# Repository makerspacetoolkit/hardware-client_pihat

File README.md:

# hardware-client_pihat
Circuit board to support the full machine client as well as simple tool that just need access control.

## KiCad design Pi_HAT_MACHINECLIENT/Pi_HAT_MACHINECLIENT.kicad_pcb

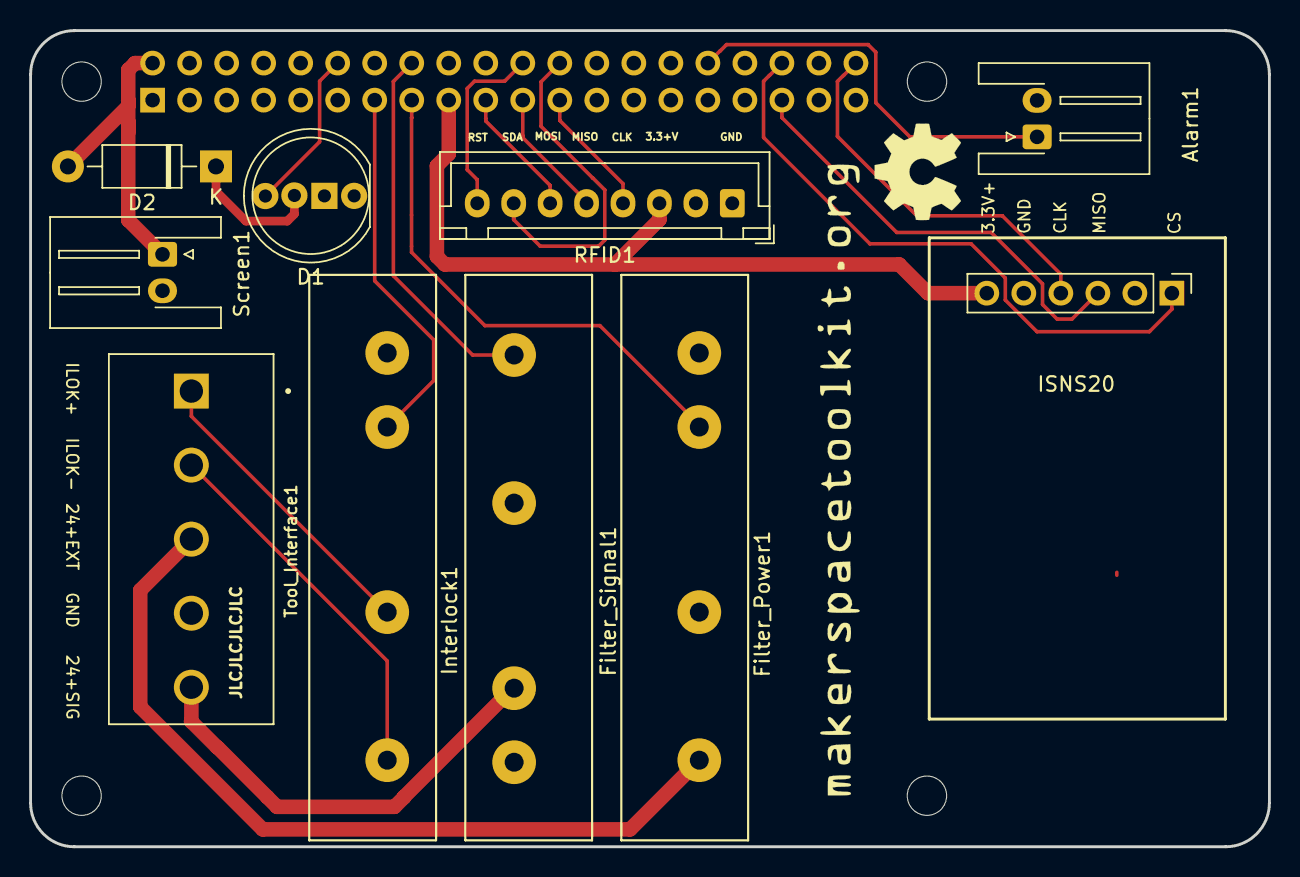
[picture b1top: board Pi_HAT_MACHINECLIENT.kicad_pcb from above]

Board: 2 copper layers, 85.0 x 56.0 mm, 11 parts (1 on the bottom side), 21 nets.

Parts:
Alarm1: Conn_01x02_Male; JST_XH_S02B-XH-A-1_1x02_P2.50mm_Horizontal
D1: WS2812B; LED_D8.0mm-ws2812
D2: 1N4001; D_DO-41_SOD81_P10.16mm_Horizontal
Filter_Power1: SSR-KF0602D; KF0602D
Filter_Signal1: SSR-KF0602D; KF0602D
ISNS20: Conn_01x06_Male; PinHeader_1x06_P2.54mm_Vertical
Interlock1: SSR-KF0602D; KF0602D
J2: Conn_02x20_Odd_Even; PinSocket_2x20_P2.54mm_Vertical
RFID1: Conn_01x08_Male; JST_XH_B08B-XH-A_1x08_P2.50mm_Vertical
Screen1: Conn_01x02_Male; JST_XH_S02B-XH-A-1_1x02_P2.50mm_Horizontal
Tool_Interface1: Screw_Terminal_01x05; CUI_TB010-508-05BE

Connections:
24V_EXT: Filter_Power1.4, Tool_Interface1.3
+3V3: ISNS20.6, J2.17, RFID1.3
+5V: D2.2, J2.2, Screen1.1
+24V: Filter_Signal1.2, Tool_Interface1.5
Alarm: Alarm1.1, J2.32
DIN: D1.4, J2.12
GND: Alarm1.2, D1.1, Filter_Power1.1, Filter_Power1.3, Filter_Signal1.1, Filter_Signal1.3, ISNS20.5, Interlock1.1, J2.25, RFID1.1, Screen1.2, Tool_Interface1.4
GPIO_22: Filter_Power1.2, J2.15
GPIO_23: Filter_Signal1.4, J2.16
GPIO_27: Interlock1.2, J2.13
Interlock+: Interlock1.4, Tool_Interface1.2
Interlock-: Interlock1.3, Tool_Interface1.1
unnamed: D1.3, D2.1
RST: J2.22, RFID1.8
SPI0_CLK: J2.23, RFID1.4
SPI0_MISO: J2.21, RFID1.5
SPI0_MOSI: J2.19, RFID1.6
SPI0_SDA: J2.24, RFID1.7
SPI1_CE2: ISNS20.1, J2.36
SPI1_CLK: ISNS20.4, J2.40
SPI1_MISO: ISNS20.3, J2.35

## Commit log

2020-05-28 Repo init

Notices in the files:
Pi_HAT_MACHINECLIENT/Pi_HAT_MACHINECLIENT.kicad_pcb:
© Peter Hartmann 2019
CC-BY-SA-4.0
